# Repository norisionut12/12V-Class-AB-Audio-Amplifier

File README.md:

# 12V Single-Supply Class AB Audio Amplifier with Speaker Protection

**Author:** Buta Noris Ionuț  

---

## Overview

This repository contains the complete hardware design, mathematical analysis, SPICE simulation validation, and physical prototype implementation of a **discrete 12V single-supply Class AB audio amplifier** with an integrated **speaker protection circuit** and **linear voltage regulator**.

Designed entirely without integrated circuits (utilizing 5 discrete bipolar junction transistors), the amplifier processes a stereo line-level input from a laptop, PC, or smartphone, sums it into a mono signal, and drives an $8\text{ }\Omega$ speaker from a standard $12\text{ V}$ DC power adapter. Because a single-rail supply biases the push-pull output stage at approximately half the supply rail ($6.76\text{ V}$ DC), a large $1000\text{ }\mu\text{F}$ output coupling capacitor is required. At power-up, charging this capacitor produces a severe transient spike ($11.6\text{ V}$ peak at $6.8\text{ ms}$). To protect the speaker voice coil and eliminate the audible turn-on "thump", an on-board RC delay circuit holds the speaker disconnected via an external relay for $\approx 0.27\text{ s}$ until the circuit settles into its DC quiescent operating point.

---

## Key Features

* **100% Discrete Analog Topology:** Built around 5 bipolar transistors (`2N2222` for small-signal amplification and switching, complementary `TIP31C` / `TIP32C` for power stages).
* **Stereo-to-Mono Input Mixer:** Passive resistive summing network ($1\text{ k}\Omega + 1\text{ k}\Omega$) providing $2\text{ k}\Omega$ inter-channel isolation and AC coupling.
* **High-Gain Voltage Amplifier Stage (VAS):** Common-emitter `2N2222` stage with AC-bypassed emitter degeneration ($A_{VAS} \approx 62$, overall $A_v \approx 51\times$ from the VAS base) and $100\text{ pF}$ Miller frequency compensation for RF immunity.
* **Diode-Biased Class AB Output Stage:** Complementary `TIP31C` (NPN) and `TIP32C` (PNP) emitter followers biased by two `1N4148` diodes ($I_Q = 8.2\text{ mA}$) to eliminate crossover dead-zones.
* **Output Zobel (Boucherot) Network:** $10\text{ }\Omega + 100\text{ nF}$ series network ($f_{Zobel} = 159\text{ kHz}$) ensuring unconditional stability when driving inductive loudspeaker loads.
* **Dedicated On-Board Linear Regulator:** Zener-referenced (`5V1` + `TIP31C`) emitter-follower regulator stepping down $12\text{ V}$ to $4.33\text{ V}$ under load to safely power the external $5\text{ V}$ relay module.
* **Active Anti-Thump Speaker Protection:** RC timing network ($\tau = 4.7\text{ s}$) driving an open-collector `2N2222` stage that delays relay actuation by $\approx 266\text{ ms}$ at power-up.
* **Custom 2-Layer THT PCB:** Manufactured with blue soldermask, wide power traces,ground plane (hatched bottom plane), and full component value silkscreen.

---

## Summary of Design Specifications

| Parameter | Design Choice / Condition | Value (Simulated / Verified at $27^\circ\text{C}$) | Circuit Reference |
| :--- | :--- | :--- | :--- |
| **Power Supply** | Single-rail standard DC adapter | $12\text{ V}$ DC, $98\text{ mA}$ total ($32\text{ mA}$ board + $66\text{ mA}$ relay) | J5, C5, C6 |
| **Speaker Load** | Capacitively coupled loudspeaker | $8\text{ }\Omega$ | C10, J2 (Relay COM-NO), J4 |
| **Audio Input** | $3.5\text{ mm}$ stereo jack summed to mono | $(V_L + V_R)/2$, $Z_{in} = 5.1\text{ k}\Omega$/channel at $1\text{ kHz}$ | J1, R2, R3, C4 |
| **Voltage Gain** | Inverting VAS + unity follower | $32.1\text{ dB}$ ($40\times$) from source; $34.2\text{ dB}$ ($51\times$) from Q2 base | Q2, R7, R8, C8 |
| **Bandwidth ($-3\text{ dB}$)** | High-pass coupling + Miller pole | $301\text{ Hz} \dots 31\text{ kHz}$ | C4, C7, C8, C10 |
| **DC Output Bias** | Near $V_{CC}/2$ | $6.76\text{ V}$ (thermal drift: $-20\text{ mV/}^\circ\text{C}$) | R4, R5, R6, R7, R8 |
| **Output Stage Bias** | Complementary Class AB push-pull | $I_Q = 8.2\text{ mA}$ | R7, D2, D3, Q3, Q4 |
| **Output Impedance** | Open-loop emitter follower | $18\text{ }\Omega$ | R7, Q3, Q4 |
| **Regulator Output** | Active-low $5\text{ V}$ relay supply | $V_Z - V_{BE1} - I_E R_E = 4.33\text{ V}$ ($5.05\text{ V}$ unloaded) | R1, D1, Q1, C2, C3 |
| **Protection Delay** | RC ramp to $V_{BE5(on)} \approx 0.66\text{ V}$ | $\tau = 4.7\text{ s} \rightarrow t_d = 0.27\text{ s}$ | R10, C11, Q5, J3 |

---

## Hardware Showcase

### Full Circuit Schematic (KiCad)

### 2D PCB Layout & 3D Visualizations
| 2D PCB Routing (Front) | 3D Rendered Top View |
| :---: | :---: |
|  |  |

| 2D PCB Traces | 3D Rendered Bottom View ("BUTA NORIS") |
| :---: | :---: |
|  |  |

### Physical Bare PCB & Assembled Prototype
| Manufactured Bare PCB (Front & Back) | Assembled Board Close-up |
| :---: | :---: |
|  |  |

---

## Repository Structure

```text
├── Docs/
│   ├── Documentatie_Romana.docx  # Comprehensive engineering report (Romanian)   
├── Fabrication_Gerbers/
│   └── gerber_files_final.zip                # Complete Gerber drill production files
├── Images/                                   # Schematic captures, renders, and photos
├── KiCad_Design_Files/
│   ├── final.kicad_pro                       # KiCad 10.0 project file
│   ├── final.kicad_sch                       # KiCad schematic sheet
│   └── final.kicad_pcb                       # KiCad PCB layout file
├── LTspice_Simulations/
│   ├── Simulare_acBode.asc                   # AC frequency sweep simulation (.ac)
│   ├── Simulare_boxa.asc                     # Large-signal transient audio simulation (.tran)
│   └── Stabilizator_12_5.asc                 # Linear regulator DC operating point simulation (.op)
├── .gitignore                                # Git ignore configuration for KiCad & LTspice cache
├── LICENSE                                   # MIT Open-Source License
├── README.md                                 # Main project showcase and technical summary
├── bill_of_materials.md                     # Categorized component table (BOM)
└── hardware_design_documentation.md          # Theoretical circuit simulation data
```

---

## Getting Started & Hardware Setup

1. **PCB Assembly:** Solder components in ascending order of profile height:
   * $0.25\text{ W}$ metal film resistors (`R1`–`R10`) and small-signal/Zener diodes (`D1`–`D3`).
   * Ceramic disc capacitors (`C1`, `C5`, `C7`, `C9`) and `TO-92` transistors (`Q2`, `Q5`).
   * Radial electrolytic capacitors (`C2`, `C3`, `C4`, `C6`, `C8`, `C10`, `C11`) — *strictly observe polarity markings on the silkscreen*.
   * Power transistors in `TO-220` packages (`Q1`, `Q3`, `Q4`).
2. **External Relay & Speaker Wiring:**
   * Connect `J3` (`J_Comanda_Releu`: `5V`, `GND`, `IN`) to the control header of a standard $5\text{ V}$ active-low relay module (`JQC-3FF-S-Z`).
   * Connect `J2` (`J_Audio`: `COM`, `NO`) to the Normally Open (NO) and Common (COM) screw terminals of the relay module.
   * Connect an $8\text{ }\Omega$ loudspeaker to terminal `J4` (`Boxa`).
3. **Power-Up:** Apply $12\text{ V}$ DC (minimum $250\text{ mA}$ capability) to connector `J5` (`Alimentare`). After $\approx 0.27\text{ s}$, the relay clicks, connecting the speaker without any audible thump.

For complete mathematical derivations, thermal drift analysis, and Safe Operating Area (SOA) verification, see [**hardware_design_documentation.md**](hardware_design_documentation.md).  
For the complete component purchasing list, see [**bill_of_materials.md**](bill_of_materials.md).

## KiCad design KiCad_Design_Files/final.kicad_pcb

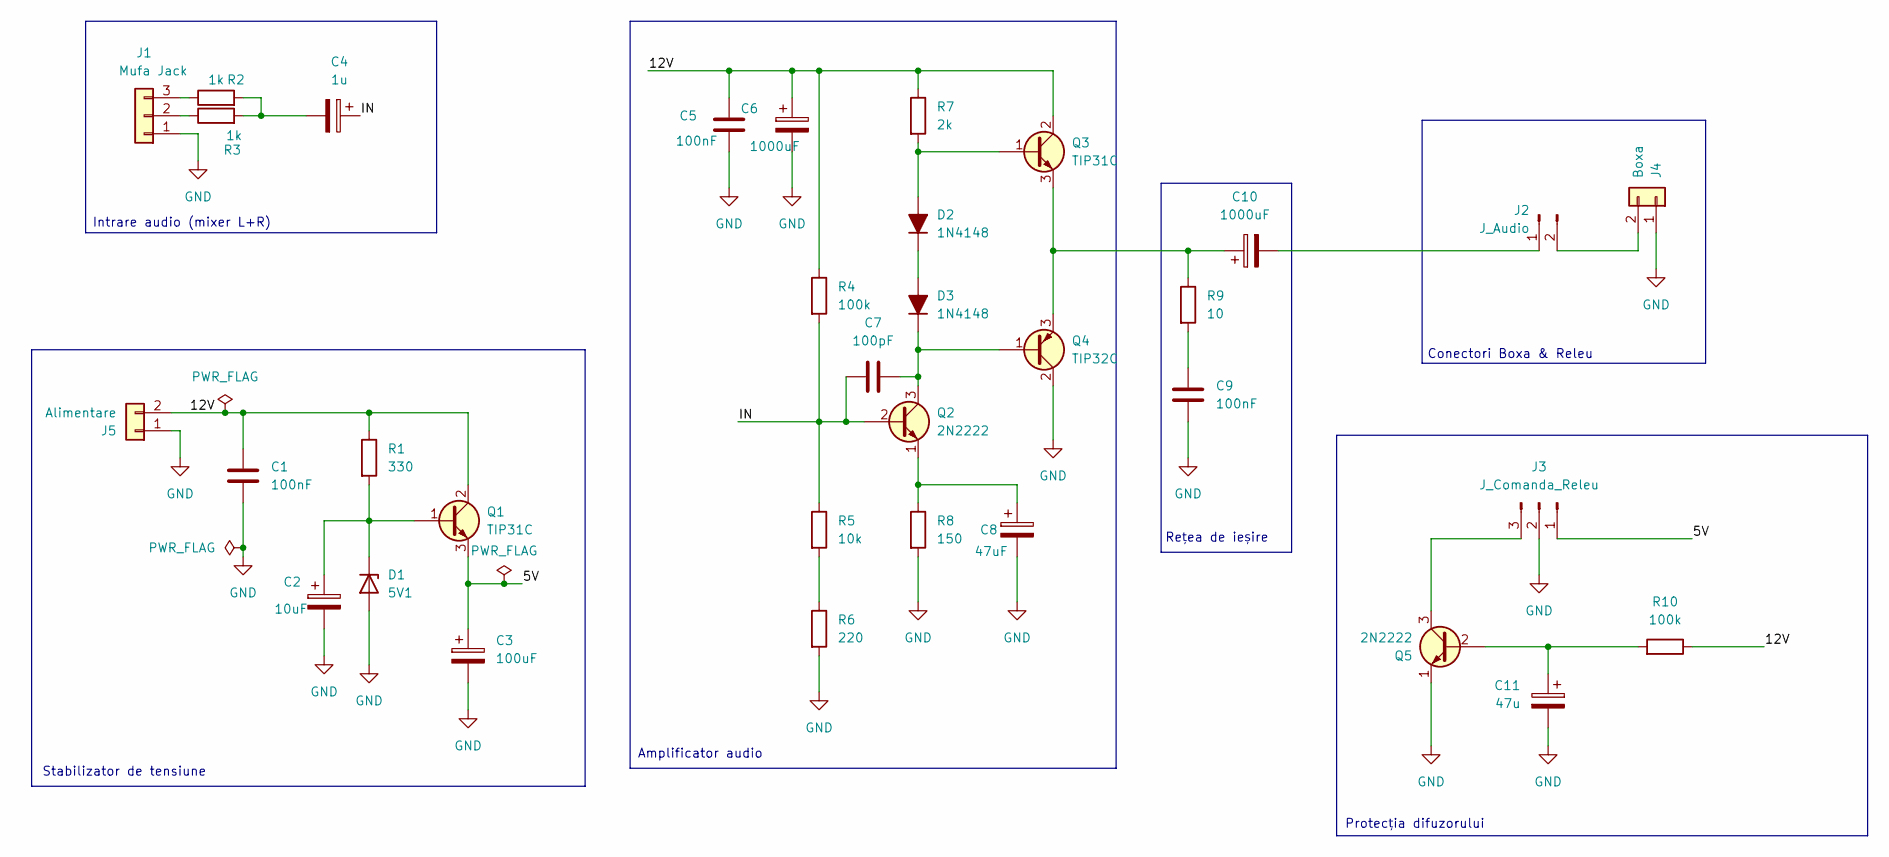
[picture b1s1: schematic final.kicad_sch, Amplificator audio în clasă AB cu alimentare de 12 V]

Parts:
C1, C5, C9: 100nF; C_Disc_D5.0mm_W2.5mm_P5.00mm
C2: 10uF; CP_Radial_D5.0mm_P2.00mm
C3: 100uF; CP_Radial_D5.0mm_P2.00mm
C4: 1u; CP_Radial_D5.0mm_P2.00mm
C6, C10: 1000uF; CP_Radial_D10.0mm_P5.00mm
C7: 100pF; C_Disc_D5.0mm_W2.5mm_P5.00mm
C8: 47uF; CP_Radial_D5.0mm_P2.00mm
C11: 47u; CP_Radial_D5.0mm_P2.00mm
D1: 5V1; D_DO-41_SOD81_P10.16mm_Horizontal
D2, D3: 1N4148; D_DO-35_SOD27_P7.62mm_Horizontal
J1: Mufa Jack; PinHeader_1x03_P2.54mm_Vertical
J2: J_Audio; PinHeader_1x02_P2.54mm_Vertical
J3: J_Comanda_Releu; PinHeader_1x03_P2.54mm_Vertical
J4: Boxa; PinHeader_1x02_P2.54mm_Vertical
J5: Alimentare; PinHeader_1x02_P2.54mm_Vertical
Q1, Q3: TIP31C; TO-220-3_Vertical
Q2, Q5: 2N2222; TO-92_Inline
Q4: TIP32C; TO-220-3_Vertical
R1: 330; R_Axial_DIN0207_L6.3mm_D2.5mm_P10.16mm_Horizontal
R2, R3: 1k; R_Axial_DIN0207_L6.3mm_D2.5mm_P10.16mm_Horizontal
R4, R10: 100k; R_Axial_DIN0207_L6.3mm_D2.5mm_P10.16mm_Horizontal
R5: 10k; R_Axial_DIN0207_L6.3mm_D2.5mm_P10.16mm_Horizontal
R6: 220; R_Axial_DIN0207_L6.3mm_D2.5mm_P10.16mm_Horizontal
R7: 2k; R_Axial_DIN0207_L6.3mm_D2.5mm_P10.16mm_Horizontal
R8: 150; R_Axial_DIN0207_L6.3mm_D2.5mm_P10.16mm_Horizontal
R9: 10; R_Axial_DIN0207_L6.3mm_D2.5mm_P10.16mm_Horizontal

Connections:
/5V: C3.1, J3.1, Q1.3 (E)
/12V: C1.1, C5.1, C6.1, J5.2, Q1.2 (C), Q3.2 (C), R1.1, R4.1, R7.1, R10.1
GND: C1.2, C2.2, C3.2, C5.2, C6.2, C8.2, C9.2, C11.2, D1.2 (A), J1.1, J3.2, J4.1, J5.1, Q4.2 (C), Q5.1 (E), R6.2, R8.2
unnamed: C4.2, R2.2, R3.2
unnamed: C9.1, R9.2
unnamed: C2.1, D1.1 (K), Q1.1 (B), R1.2
unnamed: D2.2 (A), Q3.1 (B), R7.2
unnamed: D2.1 (K), D3.2 (A)
unnamed: C7.2, D3.1 (K), Q2.3 (C), Q4.1 (B)
unnamed: J1.2, R3.1
unnamed: J1.3, R2.1
unnamed: C10.2, J2.1
unnamed: J2.2, J4.2
unnamed: J3.3, Q5.3 (C)
unnamed: C4.1, C7.1, Q2.2 (B), R4.2, R5.1
unnamed: C8.1, Q2.1 (E), R8.1
unnamed: C10.1, Q3.3 (E), Q4.3 (E), R9.1
unnamed: C11.1, Q5.2 (B), R10.2
unnamed: R5.2, R6.1

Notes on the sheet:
Stabilizator de tensiune
Protecția difuzorului
Conectori Boxa & Releu
Amplificator audio
Intrare audio (mixer L+R)
Rețea de ieșire

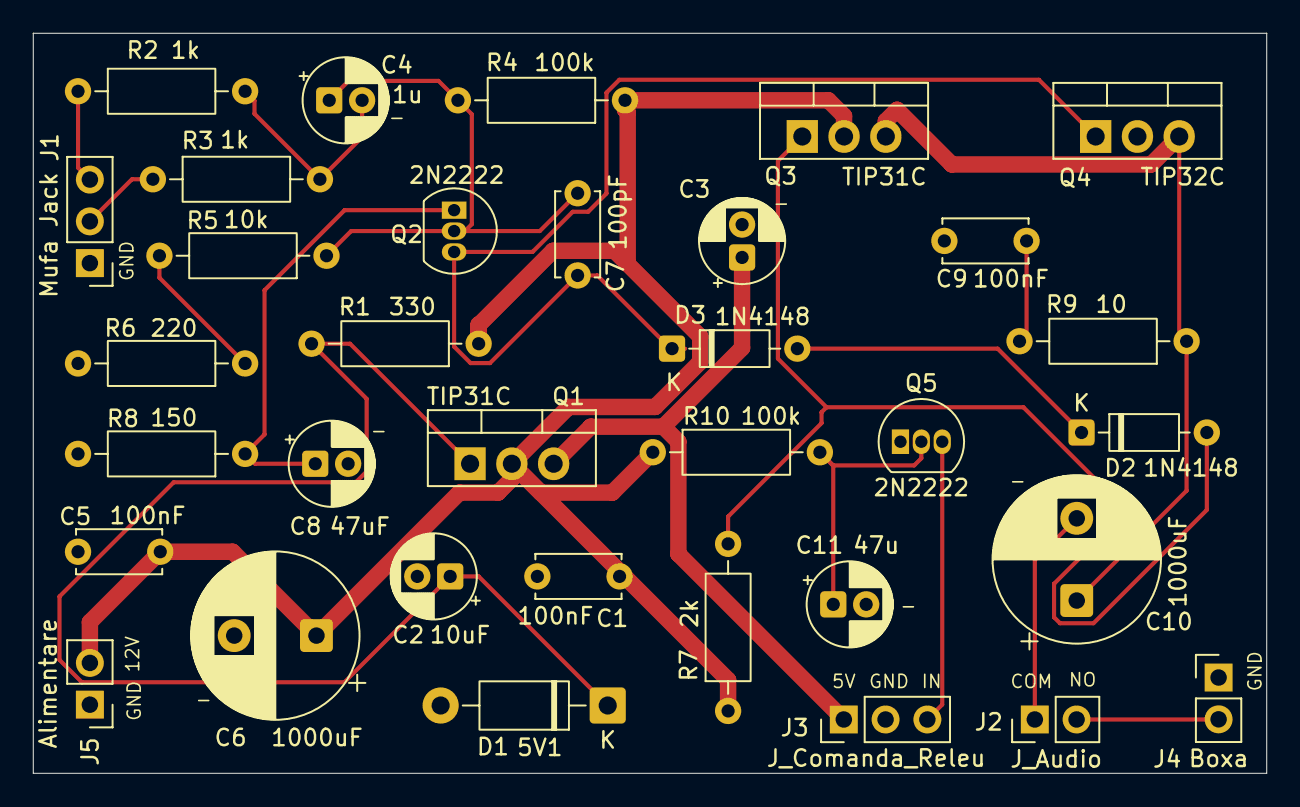
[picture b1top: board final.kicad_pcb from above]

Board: 2 copper layers, 75.0 x 45.0 mm, 34 parts (0 on the bottom side), 19 nets.
